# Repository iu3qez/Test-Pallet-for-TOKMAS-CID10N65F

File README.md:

Test Pallet for TOKMAS GaN CID10N65F transistor.
Inspired from QRP Labs design, should be using the same heatsink of QRP Labs 50 Watt Amplifier.
Board ordered to JLCPB

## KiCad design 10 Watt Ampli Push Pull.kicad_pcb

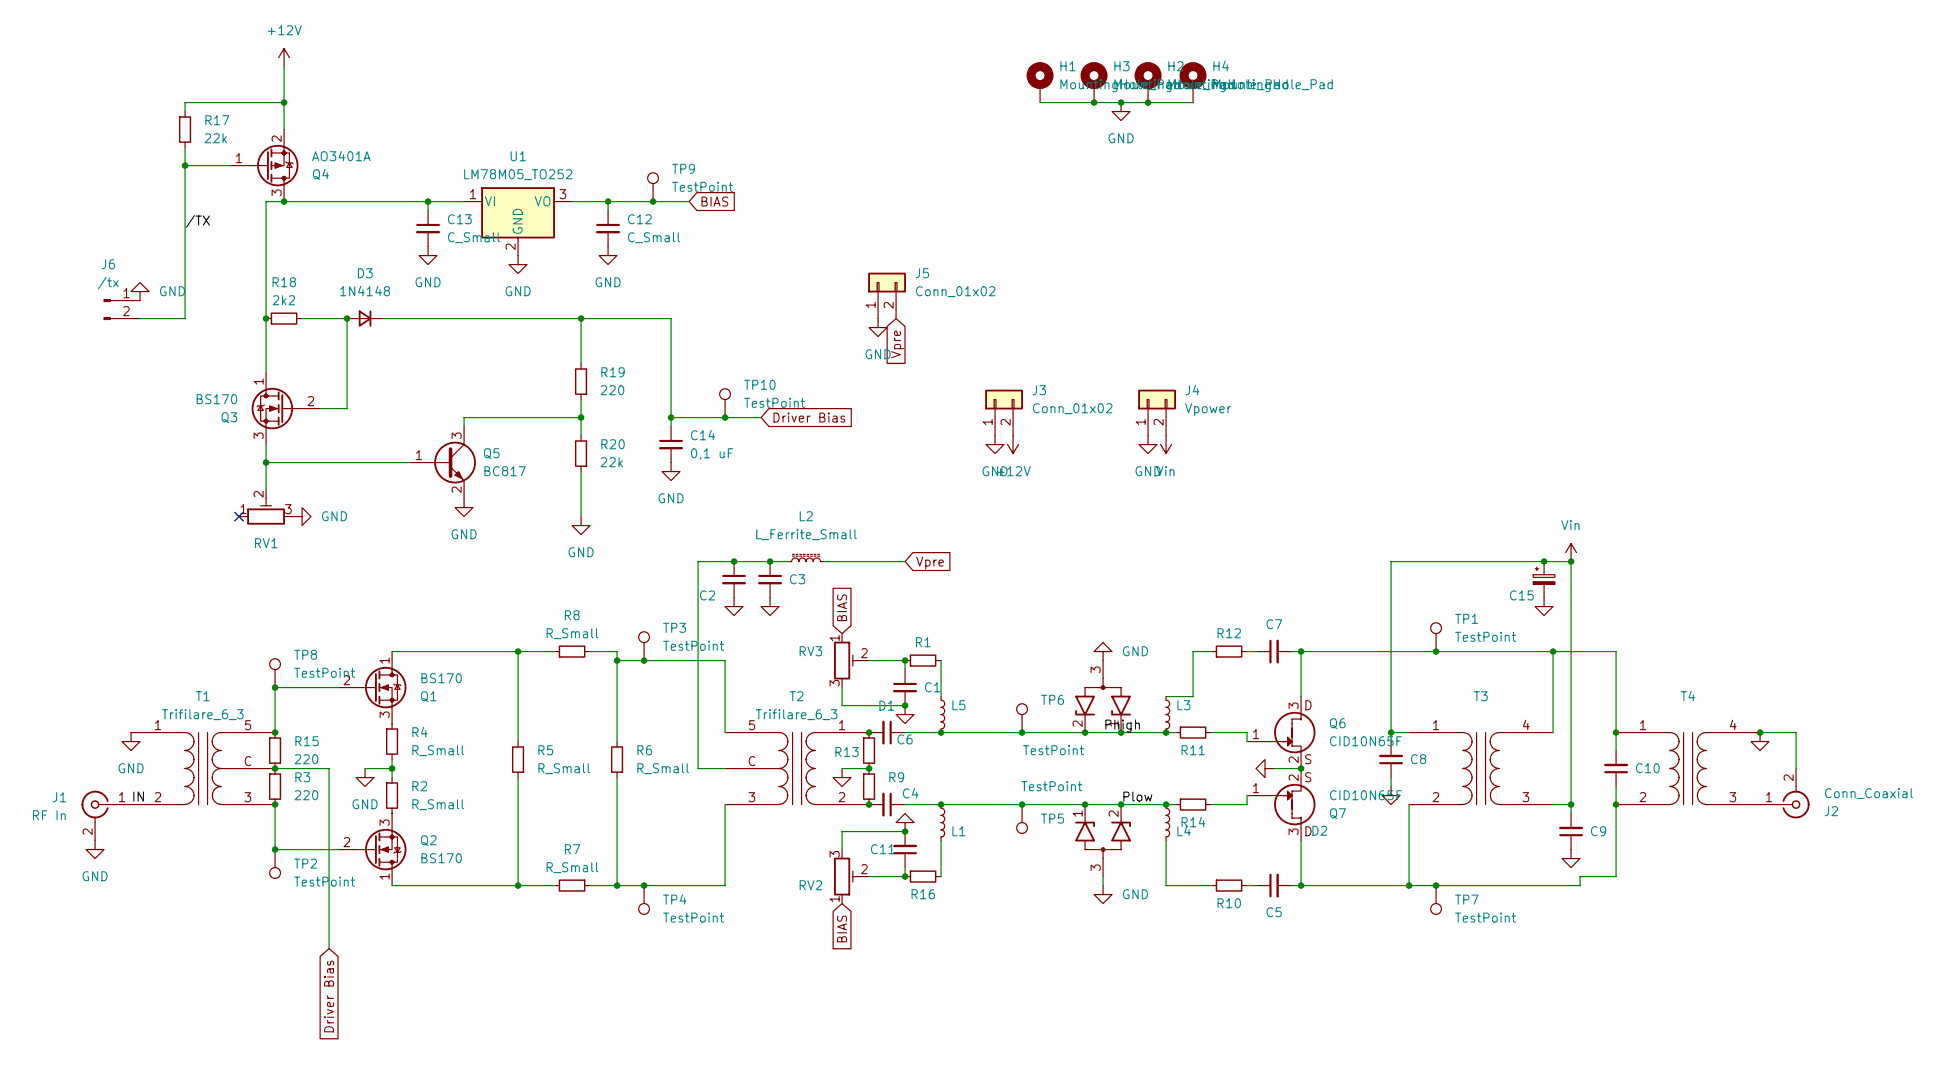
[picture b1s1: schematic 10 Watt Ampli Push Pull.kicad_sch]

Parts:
C1, C5, C6, C7, C11: C_Small; C_0805_2012Metric
C2: 10uF X7R; C_0805_2012Metric_Pad1.18x1.45mm_HandSolder
C3: 0,1uF; C_0805_2012Metric
C4: C_Small; C_0805_2012Metric_Pad1.18x1.45mm_HandSolder
C8: 100 V; C_1206_3216Metric_Pad1.33x1.80mm_HandSolder
C9: C_Small 100V; C_1206_3216Metric_Pad1.33x1.80mm_HandSolder
C10: C_Small; C_1206_3216Metric_Pad1.33x1.80mm_HandSolder
C12, C13: C_Small; C_0603_1608Metric
C14: 0,1 uF; C_0603_1608Metric
C15: 100uF 80V; CP_Radial_D10.0mm_P5.00mm
D1, D2: RCLAMP0502B; SOT-416
D3: 1N4148; D_SOD-123
H1, H2, H3, H4: MountingHole_Pad; MountingHole_3.2mm_M3_Pad_Via
J1: RF In; BNC_TEConnectivity_1478204_Vertical
J2: Conn_Coaxial; BNC_TEConnectivity_1478204_Vertical
J3, J5: Conn_01x02; JST_XH_B2B-XH-AM_1x02_P2.50mm_Vertical
J4: Vpower; JST_XH_B2B-XH-AM_1x02_P2.50mm_Vertical
J6: /tx; JST_XH_B2B-XH-AM_1x02_P2.50mm_Vertical
L1, L3, L4, L5: 1uF; L_0805_2012Metric
L2: L_Ferrite_Small; T37
Q1, Q2, Q3: BS170; TO-92_Inline
Q4: AO3401A; SOT-23
Q5: BC817; SOT-23
Q6, Q7: CID10N65F; TO-220-3_Vertical
R1, R9: 220; C_0805_2012Metric
R2, R4: R_Small; R_0603_1608Metric
R3, R15, R19: 220; R_0603_1608Metric
R5: R_Small; R_0805_2012Metric
R6, R7, R8: R_Small; C_0805_2012Metric
R10, R12: 220; R_1206_3216Metric
R11, R14: 0; R_0805_2012Metric
R13, R16: 220; R_0805_2012Metric
R17, R20: 22k; R_0603_1608Metric
R18: 2k2; R_0603_1608Metric
RV1: 100 ohm; Potentiometer_Bourns_3006P_Horizontal
RV2, RV3: R_Potentiometer_Trim; Potentiometer_Bourns_3006P_Horizontal
T1, T2: Trifilare_6_3; TR_3x3_FT50
T3: Transformer_1P_1S; TR_2x2_FT50
T4: Transformer_1P_1S; doppio_tubo
TP1, TP2, TP3, TP4, TP5, TP6, TP7, TP8, TP9, TP10: TestPoint; TestPoint_Loop_D2.50mm_Drill1.0mm_LowProfile
U1: LM78M05_TO252; TO-252-2

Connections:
+12V: J3.2, Q4.2 (S), R17.1
/IN: J1.1 (In), T1.2 (AB)
/Phigh: C6.1, D1.1 (K1), D1.2 (K2), L3.2, L5.2, R11.1, TP6.1
/Plow: C4.1, D2.1 (K1), D2.2 (K2), L1.2, L4.2, R14.1, TP5.1
//TX: J6.2, Q4.1 (G), R17.2
BIAS: C12.1, RV2.1, RV3.1, TP9.1, U1.3 (VO)
Driver Bias: C14.1, D3.1 (K), R3.1, R15.2, R19.2, T1.C (SC), TP10.1
GND: C1.2, C2.2, C3.2, C8.1, C9.1, C11.2, C12.2, C13.2, C14.2, C15.2, D1.3 (A), D2.3 (A), H1.1, H2.1, H3.1, H4.1, J1.2 (Ext), J2.2 (Ext), J3.1, J4.1, J5.1, J6.1, Q5.2 (E), Q6.2 (S), Q7.2 (S), R2.1, R4.2, R9.1, R13.2, R20.1, RV1.3, RV2.3, RV3.3, T1.1 (AA), T4.4 (SB), U1.2 (GND)
unnamed: C1.1, R1.1, RV3.2
unnamed: C5.1, R10.2
unnamed: C7.1, R12.2
unnamed: C11.1, R16.1, RV2.2
unnamed: D3.2 (A), Q3.2 (G), R18.2
unnamed: J2.1 (In), T4.3 (SA)
unnamed: L1.1, R16.2
unnamed: L3.1, R12.1
unnamed: L4.1, R10.1
unnamed: L5.1, R1.2
unnamed: Q1.1 (D), R5.2, R8.1
unnamed: Q1.2 (G), R15.1, T1.5 (SB), TP8.1
unnamed: Q1.3 (S), R4.1
unnamed: Q2.1 (D), R5.1, R7.2
unnamed: Q2.2 (G), R3.2, T1.3 (SA), TP2.1
unnamed: Q2.3 (S), R2.2
unnamed: C13.1, Q3.1 (D), Q4.3 (D), R18.1, U1.1 (VI)
unnamed: Q3.3 (S), Q5.1 (B), RV1.2
unnamed: Q5.3 (C), R19.1, R20.2
unnamed: C7.2, C10.2, Q6.3 (D), T3.4 (SB), T4.1 (AA), TP1.1
unnamed: Q6.1 (G), R11.2
unnamed: C5.2, C10.1, Q7.3 (D), T3.2 (AB), T4.2 (AB), TP7.1
unnamed: Q7.1 (G), R14.2
unnamed: C6.2, R13.1, T2.1 (AA)
unnamed: C4.2, R9.2, T2.2 (AB)
unnamed: R6.1, R7.1, T2.3 (SA), TP4.1
unnamed: R6.2, R8.2, T2.5 (SB), TP3.1
unnamed: C2.1, C3.1, L2.1, T2.C (SC)
Vin: C8.2, C9.2, C15.1, J4.2, T3.1 (AA), T3.3 (SA)
Vpre: J5.2, L2.2

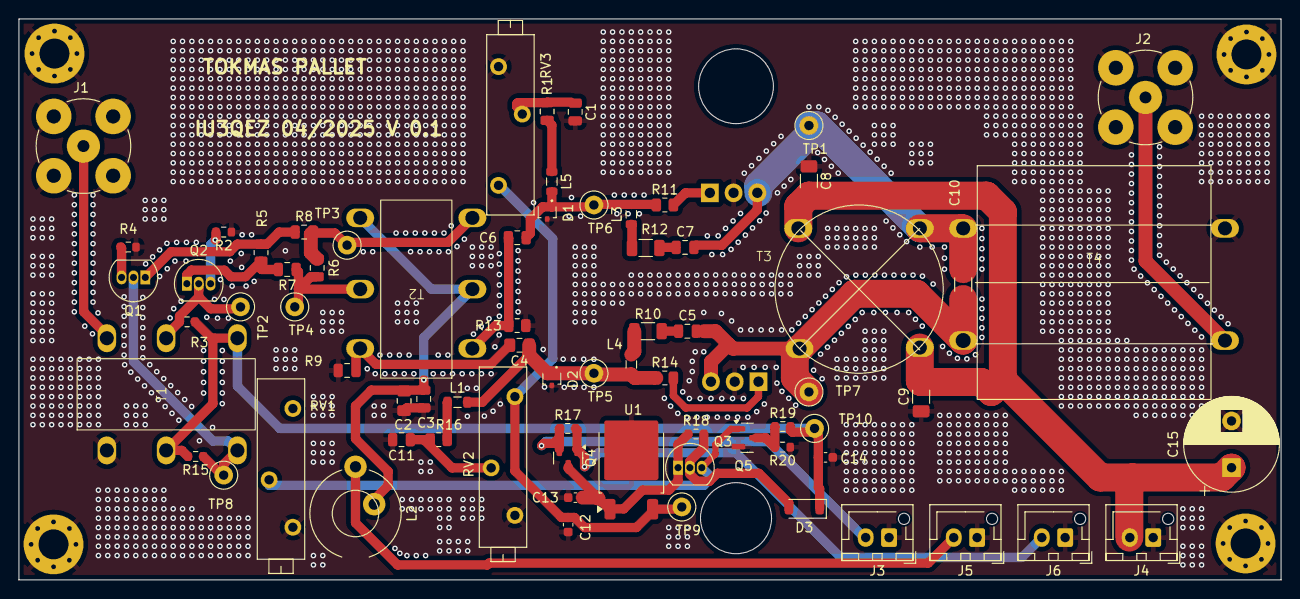
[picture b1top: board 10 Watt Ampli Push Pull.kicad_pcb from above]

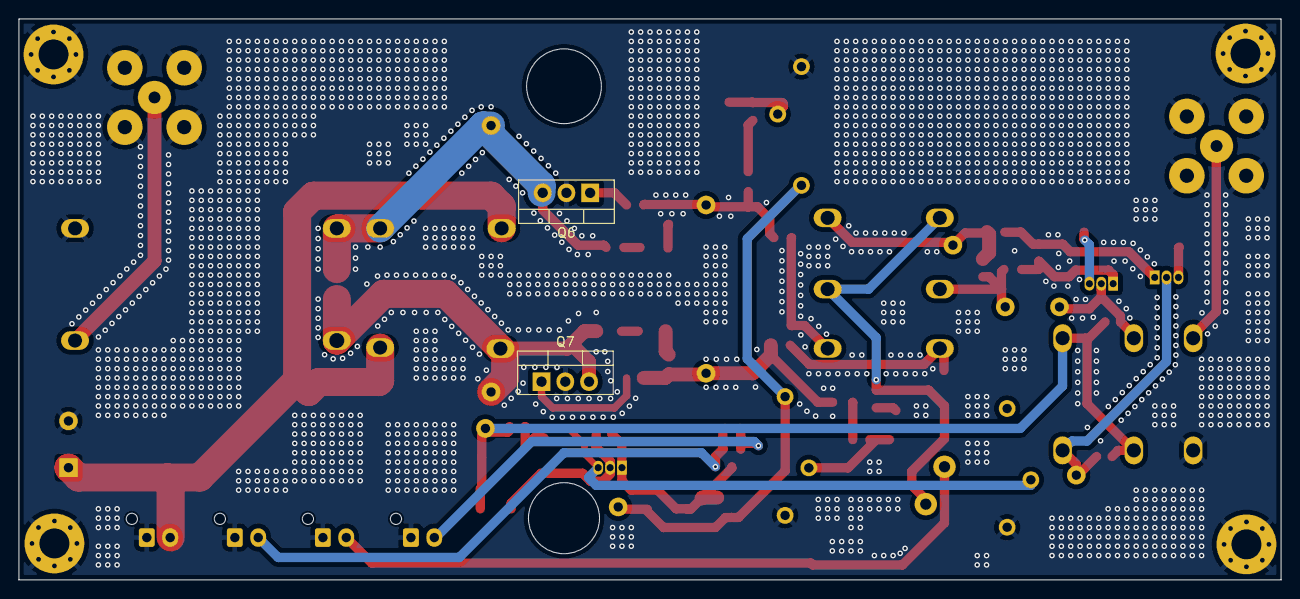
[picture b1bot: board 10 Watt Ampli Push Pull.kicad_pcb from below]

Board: 2 copper layers, 135.0 x 60.0 mm, 78 parts (2 on the bottom side), 38 nets.

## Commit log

2025-04-30 First commit. JLCPC
